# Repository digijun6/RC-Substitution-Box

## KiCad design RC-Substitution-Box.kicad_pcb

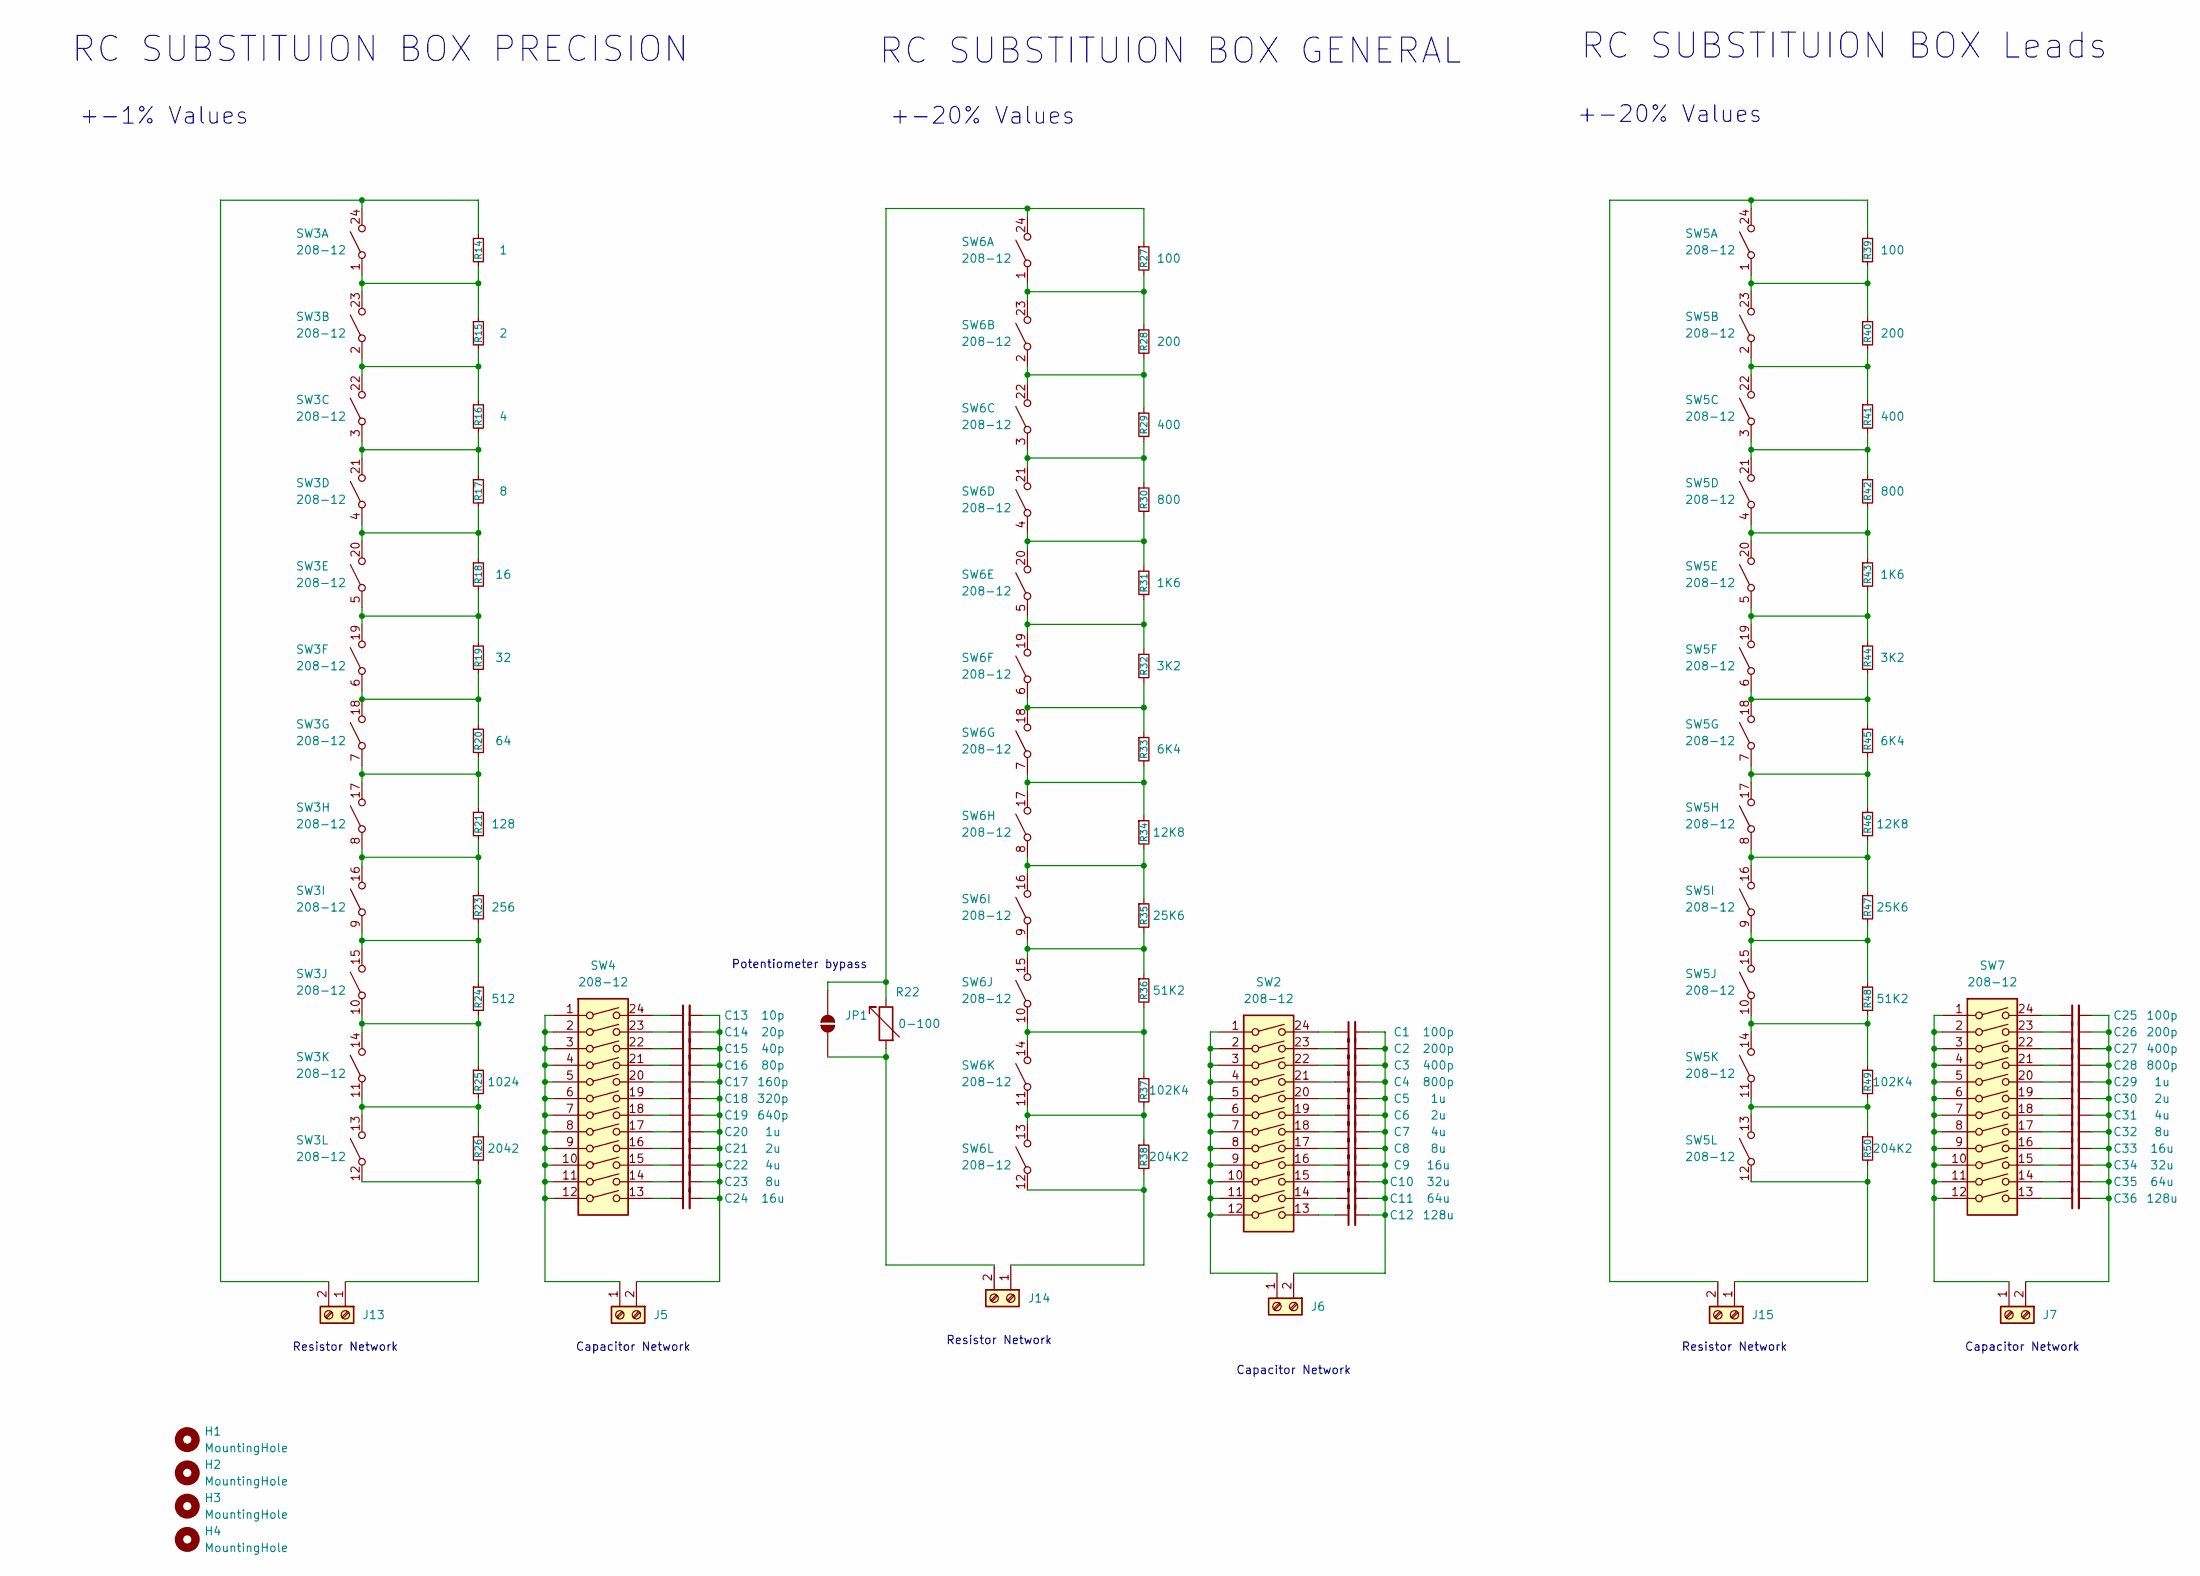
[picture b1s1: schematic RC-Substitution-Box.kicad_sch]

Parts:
C1: 100p; C_0603_1608Metric
C2: 200p; C_0603_1608Metric
C3: 400p; C_0603_1608Metric
C4: 800p; C_0603_1608Metric
C5: 1u; C_0603_1608Metric
C6: 2u; C_0603_1608Metric
C7: 4u; C_0603_1608Metric
C8: 8u; C_0603_1608Metric
C9: 16u; C_0603_1608Metric
C10: 32u; C_0603_1608Metric
C11: 64u; C_0603_1608Metric
C12: 128u; C_0603_1608Metric
C13: 10p; C_0402_1005Metric
C14: 20p; C_0402_1005Metric
C15: 40p; C_0402_1005Metric
C16: 80p; C_0402_1005Metric
C17: 160p; C_0402_1005Metric
C18: 320p; C_0402_1005Metric
C19: 640p; C_0402_1005Metric
C20: 1u; C_0402_1005Metric
C21: 2u; C_0402_1005Metric
C22: 4u; C_0402_1005Metric
C23: 8u; C_0402_1005Metric
C24: 16u; C_0402_1005Metric
C25: 100p; C_Disc_D5.1mm_W3.2mm_P5.00mm
C26: 200p; C_Disc_D5.1mm_W3.2mm_P5.00mm
C27: 400p; C_Disc_D5.1mm_W3.2mm_P5.00mm
C28: 800p; C_Disc_D5.1mm_W3.2mm_P5.00mm
C29: 1u; C_Disc_D5.1mm_W3.2mm_P5.00mm
C30: 2u; C_Disc_D5.1mm_W3.2mm_P5.00mm
C31: 4u; C_Disc_D5.1mm_W3.2mm_P5.00mm
C32: 8u; C_Disc_D5.1mm_W3.2mm_P5.00mm
C33: 16u; C_Disc_D5.1mm_W3.2mm_P5.00mm
C34: 32u; C_Disc_D5.1mm_W3.2mm_P5.00mm
C35: 64u; C_Disc_D5.1mm_W3.2mm_P5.00mm
C36: 128u; C_Disc_D5.1mm_W3.2mm_P5.00mm
H1, H2, H3, H4: MountingHole; MountingHole_3.2mm_M3_Pad
J5, J6, J7, J13, J14, J15: Screw_Terminal_01x02; TerminalBlock_Phoenix_MKDS-1,5-2_1x02_P5.00mm_Horizontal
JP1: SolderJumper_2_Open; SolderJumper-2_P1.3mm_Open_Pad1.0x1.5mm
R14: 1; R_0402_1005Metric
R15: 2; R_0402_1005Metric
R16: 4; R_0402_1005Metric
R17: 8; R_0402_1005Metric
R18: 16; R_0402_1005Metric
R19: 32; R_0402_1005Metric
R20: 64; R_0402_1005Metric
R21: 128; R_0402_1005Metric
R22: 0-100; RES-ADJ-TH_3P-L9.5-W9.5-P2.54-BR-BS
R23: 256; R_0402_1005Metric
R24: 512; R_0402_1005Metric
R25: 1024; R_0402_1005Metric
R26: 2042; R_0402_1005Metric
R27: 100; R_0603_1608Metric
R28: 200; R_0603_1608Metric
R29: 400; R_0603_1608Metric
R30: 800; R_0603_1608Metric
R31: 1K6; R_0603_1608Metric
R32: 3K2; R_0603_1608Metric
R33: 6K4; R_0603_1608Metric
R34: 12K8; R_0603_1608Metric
R35: 25K6; R_0603_1608Metric
R36: 51K2; R_0603_1608Metric
R37: 102K4; R_0603_1608Metric
R38: 204K2; R_0603_1608Metric
R39: 100; R_Axial_DIN0207_L6.3mm_D2.5mm_P7.62mm_Horizontal
R40: 200; R_Axial_DIN0207_L6.3mm_D2.5mm_P7.62mm_Horizontal
R41: 400; R_Axial_DIN0207_L6.3mm_D2.5mm_P7.62mm_Horizontal
R42: 800; R_Axial_DIN0207_L6.3mm_D2.5mm_P7.62mm_Horizontal
R43: 1K6; R_Axial_DIN0207_L6.3mm_D2.5mm_P7.62mm_Horizontal
R44: 3K2; R_Axial_DIN0207_L6.3mm_D2.5mm_P7.62mm_Horizontal
R45: 6K4; R_Axial_DIN0207_L6.3mm_D2.5mm_P7.62mm_Horizontal
R46: 12K8; R_Axial_DIN0207_L6.3mm_D2.5mm_P7.62mm_Horizontal
R47: 25K6; R_Axial_DIN0207_L6.3mm_D2.5mm_P7.62mm_Horizontal
R48: 51K2; R_Axial_DIN0207_L6.3mm_D2.5mm_P7.62mm_Horizontal
R49: 102K4; R_Axial_DIN0207_L6.3mm_D2.5mm_P7.62mm_Horizontal
R50: 204K2; R_Axial_DIN0207_L6.3mm_D2.5mm_P7.62mm_Horizontal
SW2, SW3, SW4, SW5, SW6, SW7: 208-12; SW_DIP_SPSTx12_Slide_9.78x32.66mm_W7.62mm_P2.54mm

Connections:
unnamed: C1.1, SW2.24
unnamed: C2.1, SW2.23
unnamed: C3.1, SW2.22
unnamed: C4.1, SW2.21
unnamed: C5.1, SW2.20
unnamed: C6.1, SW2.19
unnamed: C7.1, SW2.18
unnamed: C8.1, SW2.17
unnamed: C9.1, SW2.16
unnamed: C10.1, SW2.15
unnamed: C11.1, SW2.14
unnamed: C12.1, SW2.13
unnamed: C13.1, SW4.24
unnamed: C14.1, SW4.23
unnamed: C15.1, SW4.22
unnamed: C16.1, SW4.21
unnamed: C17.1, SW4.20
unnamed: C18.1, SW4.19
unnamed: C19.1, SW4.18
unnamed: C20.1, SW4.17
unnamed: C21.1, SW4.16
unnamed: C22.1, SW4.15
unnamed: C23.1, SW4.14
unnamed: C24.1, SW4.13
unnamed: C25.1, SW7.24
unnamed: C26.1, SW7.23
unnamed: C27.1, SW7.22
unnamed: C28.1, SW7.21
unnamed: C29.1, SW7.20
unnamed: C30.1, SW7.19
unnamed: C31.1, SW7.18
unnamed: C32.1, SW7.17
unnamed: C33.1, SW7.16
unnamed: C34.1, SW7.15
unnamed: C35.1, SW7.14
unnamed: C36.1, SW7.13
unnamed: J5.1, SW4.1, SW4.2, SW4.3, SW4.4, SW4.5, SW4.6, SW4.7, SW4.8, SW4.9, SW4.10, SW4.11, SW4.12
unnamed: C13.2, C14.2, C15.2, C16.2, C17.2, C18.2, C19.2, C20.2, C21.2, C22.2, C23.2, C24.2, J5.2
unnamed: J6.1, SW2.1, SW2.2, SW2.3, SW2.4, SW2.5, SW2.6, SW2.7, SW2.8, SW2.9, SW2.10, SW2.11, SW2.12
unnamed: C1.2, C2.2, C3.2, C4.2, C5.2, C6.2, C7.2, C8.2, C9.2, C10.2, C11.2, C12.2, J6.2
unnamed: J7.1, SW7.1, SW7.2, SW7.3, SW7.4, SW7.5, SW7.6, SW7.7, SW7.8, SW7.9, SW7.10, SW7.11, SW7.12
unnamed: C25.2, C26.2, C27.2, C28.2, C29.2, C30.2, C31.2, C32.2, C33.2, C34.2, C35.2, C36.2, J7.2
unnamed: J13.1, R26.2, SW3.12
unnamed: J13.2, R14.1, SW3.24
unnamed: J14.1, R38.2, SW6.12
unnamed: J14.2, JP1.1 (A), R22.2
unnamed: J15.1, R50.2, SW5.12
unnamed: J15.2, R39.1, SW5.24
unnamed: JP1.2 (B), R22.1, R27.1, SW6.24
unnamed: R14.2, R15.1, SW3.1, SW3.23
unnamed: R15.2, R16.1, SW3.2, SW3.22
unnamed: R16.2, R17.1, SW3.3, SW3.21
unnamed: R17.2, R18.1, SW3.4, SW3.20
unnamed: R18.2, R19.1, SW3.5, SW3.19
unnamed: R19.2, R20.1, SW3.6, SW3.18
unnamed: R20.2, R21.1, SW3.7, SW3.17
unnamed: R21.2, R23.1, SW3.8, SW3.16
unnamed: R23.2, R24.1, SW3.9, SW3.15
unnamed: R24.2, R25.1, SW3.10, SW3.14
unnamed: R25.2, R26.1, SW3.11, SW3.13
unnamed: R27.2, R28.1, SW6.1, SW6.23
unnamed: R28.2, R29.1, SW6.2, SW6.22
unnamed: R29.2, R30.1, SW6.3, SW6.21
unnamed: R30.2, R31.1, SW6.4, SW6.20
unnamed: R31.2, R32.1, SW6.5, SW6.19
unnamed: R32.2, R33.1, SW6.6, SW6.18
unnamed: R33.2, R34.1, SW6.7, SW6.17
unnamed: R34.2, R35.1, SW6.8, SW6.16
unnamed: R35.2, R36.1, SW6.9, SW6.15
unnamed: R36.2, R37.1, SW6.10, SW6.14
unnamed: R37.2, R38.1, SW6.11, SW6.13
unnamed: R39.2, R40.1, SW5.1, SW5.23
unnamed: R40.2, R41.1, SW5.2, SW5.22
unnamed: R41.2, R42.1, SW5.3, SW5.21
unnamed: R42.2, R43.1, SW5.4, SW5.20
unnamed: R43.2, R44.1, SW5.5, SW5.19
unnamed: R44.2, R45.1, SW5.6, SW5.18
unnamed: R45.2, R46.1, SW5.7, SW5.17
unnamed: R46.2, R47.1, SW5.8, SW5.16
unnamed: R47.2, R48.1, SW5.9, SW5.15
unnamed: R48.2, R49.1, SW5.10, SW5.14
unnamed: R49.2, R50.1, SW5.11, SW5.13

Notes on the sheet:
+-1% Values
Resistor Network
+-20% Values
Capacitor Network
RC SUBSTITUION BOX Leads
Potentiometer bypass
RC SUBSTITUION BOX PRECISION
RC SUBSTITUION BOX GENERAL

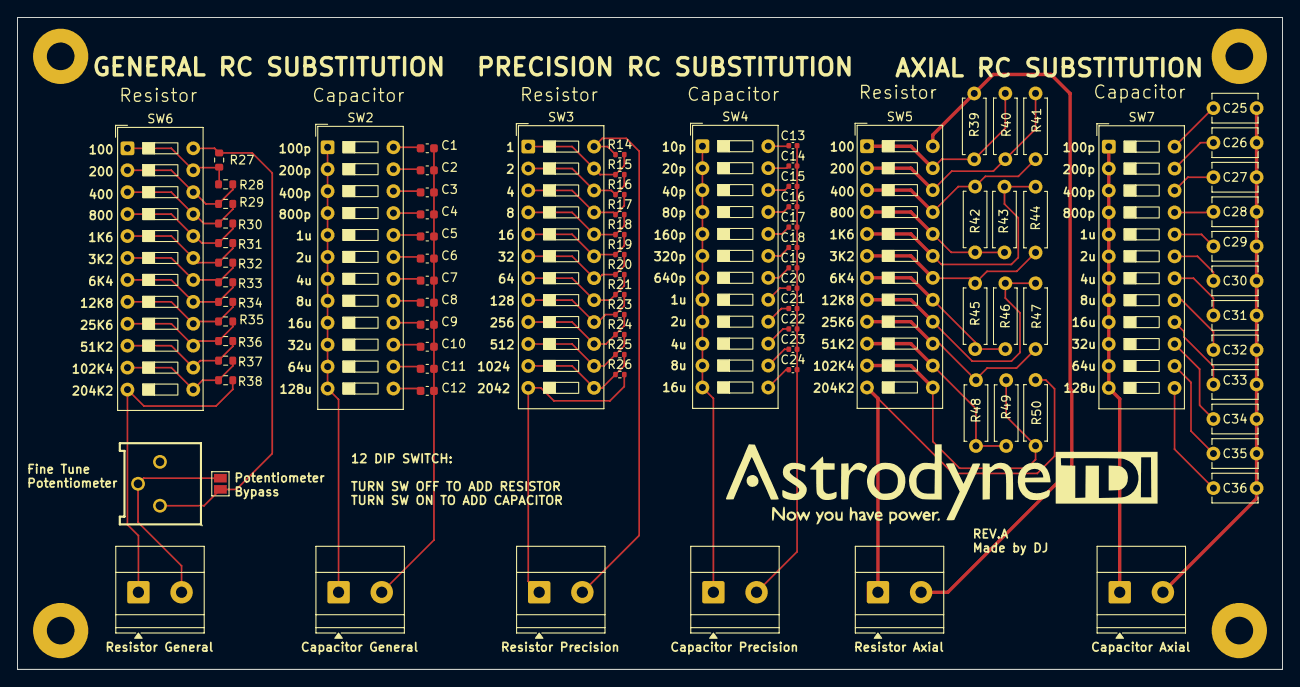
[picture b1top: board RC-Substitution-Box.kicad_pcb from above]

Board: 2 copper layers, 146.5 x 75.5 mm, 90 parts (0 on the bottom side), 82 nets.

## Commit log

2026-04-27 PCB LAYOUT DONE
2026-05-04 Removing SW and adding Axial RC Option
    -Removing the SW becasue it is not needed
    - Adding an axial option just for flexibility
2026-05-05 updated layout
2026-05-06 Finished Tracing + DRC Check
2026-05-10 GBRL Files
2026-05-15 Fix silkscreen labeling
    -Values are too high
